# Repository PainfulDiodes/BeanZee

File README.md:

# BeanZee Z80 homebrew development board
A small Z80 based single-board-computer designed for experimentation.

Z80 CPU, 10 MHz clock, a simple reset circuit, 32K ROM, 32K RAM, FTDI UM245R USB module and the necessary glue logic.

Connectors provided for interfacing with the Z80: address, data, read, write, IO request, memory request, clock and reset.

The internal clock may be overridden by an external clock, and the internal memory and USB module may also be disabled via jumpers so that external devices can be used, or additional memory and IO selection logic added.

There is an accompanying [Marvin](https://github.com/PainfulDiodes/marvin) simple monitor program which can be used to inspect and modify memory contents and load and execute a program from the host computer. Example programs can be found in [BeanZeeBytes](https://github.com/PainfulDiodes/BeanZeeBytes).

See also:  
* [Detailed README](README-DETAILED.md)   
* [QWERTY Keyboard, simple LCD display and GPIO for BeanZee](https://github.com/PainfulDiodes/BeanBoard)  
* [MINT minimalist interpreter for BeanZee](https://github.com/PainfulDiodes/MINT)  
* [Blog post](https://painfuldiodes.wordpress.com/2024/12/29/beanzee-z80-development-board/)  
* [Hackaday project](https://hackaday.io/project/202193-beanzee)  
    
<br>
<br>

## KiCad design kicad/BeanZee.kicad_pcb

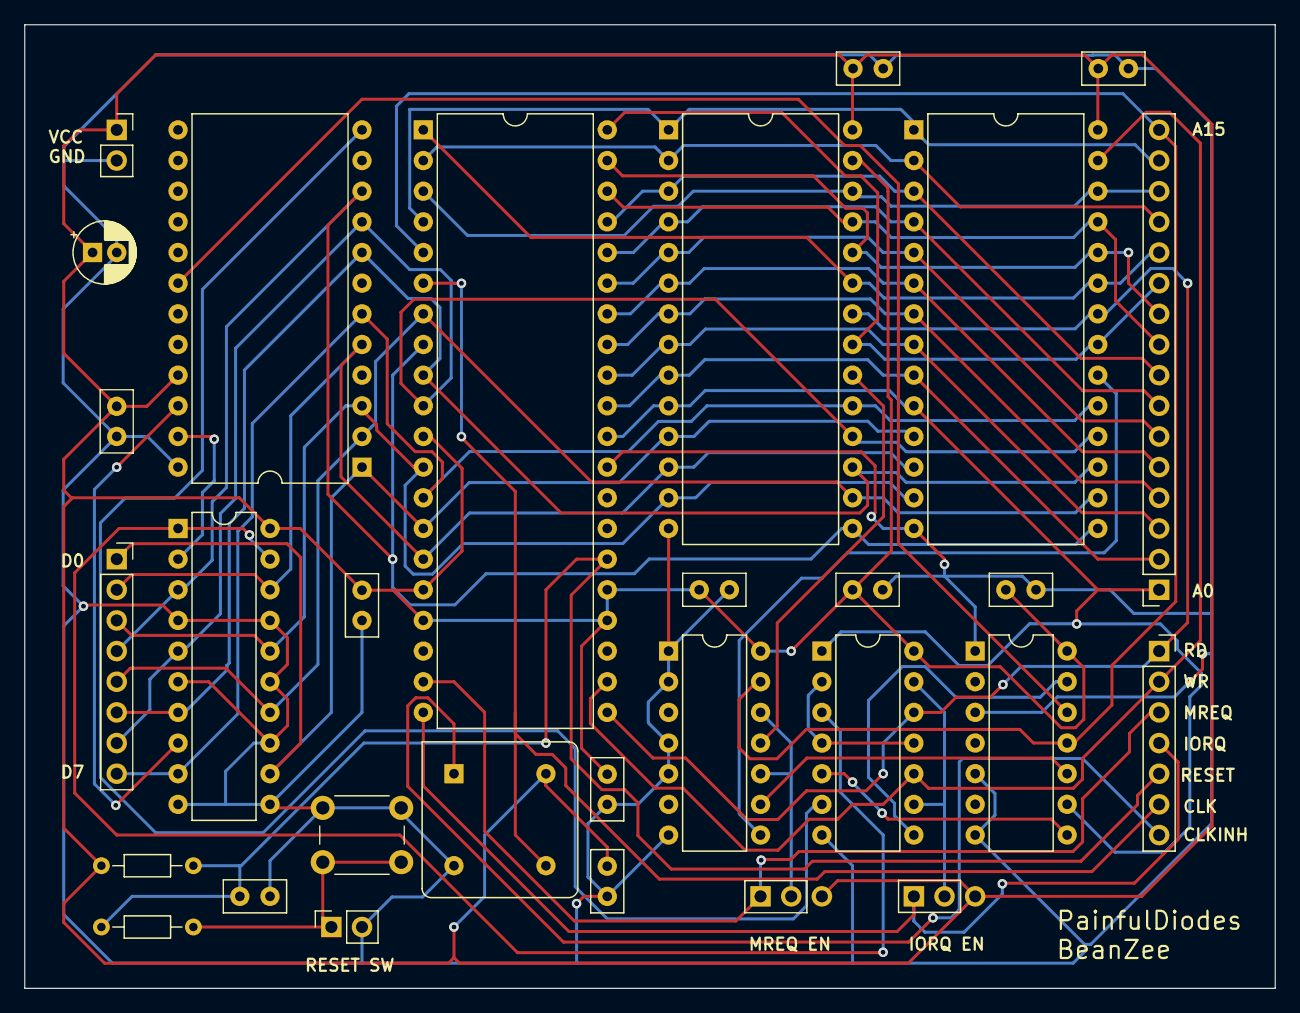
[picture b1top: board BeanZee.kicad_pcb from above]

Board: 2 copper layers, 103.6 x 79.8 mm, 30 parts (0 on the bottom side), 47 nets.

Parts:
C1, C2, C4, C5, C6, C7, C8, C9, C10, C11: 0.1uF; C_Disc_D5.0mm_W2.5mm_P2.50mm
C3: 100uF; CP_Radial_D5.0mm_P2.00mm
J1: Address; PinSocket_1x16_P2.54mm_Vertical
J2: Data; PinSocket_1x08_P2.54mm_Vertical
J3: Control; PinSocket_1x07_P2.54mm_Vertical
J4: Power; PinSocket_1x02_P2.54mm_Vertical
J5: Reset; PinSocket_1x02_P2.54mm_Vertical
JP1: IORQ_enable; PinHeader_1x03_P2.54mm_Vertical
JP2: MREQ_enable; PinHeader_1x03_P2.54mm_Vertical
R1: 220R; R_Axial_DIN0204_L3.6mm_D1.6mm_P7.62mm_Horizontal
R2: 10k; R_Axial_DIN0204_L3.6mm_D1.6mm_P7.62mm_Horizontal
SW1: Reset; SW_PUSH_6mm_H5mm
U1: 74LS244; DIP-20_W7.62mm
U2, U4: 74LS32; DIP-14_W7.62mm
U3: 74LS04; DIP-14_W7.62mm
U5: Z80CPU; DIP-40_W15.24mm
U6: AT28C256 (32kB ROM); DIP-28_W15.24mm
U7: UM245R; DIP-24_W15.24mm
U8: ECS-2200B-100 10MHz; Oscillator_DIP-8
U9: AS6C62256 (32kB SRAM); DIP-28_W15.24mm

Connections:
/A0: J1.1, U3.9, U4.1, U5.30 (A0), U6.10 (A0), U9.10 (A0)
/A1: J1.2, U5.31 (A1), U6.9 (A1), U9.9 (A1)
/A2: J1.3, U5.32 (A2), U6.8 (A2), U9.8 (A2)
/A3: J1.4, U5.33 (A3), U6.7 (A3), U9.7 (A3)
/A4: J1.5, U5.34 (A4), U6.6 (A4), U9.6 (A4)
/A5: J1.6, U5.35 (A5), U6.5 (A5), U9.5 (A5)
/A6: J1.7, U5.36 (A6), U6.4 (A6), U9.4 (A6)
/A7: J1.8, U5.37 (A7), U6.3 (A7), U9.3 (A7)
/A8: J1.9, U5.38 (A8), U6.25 (A8), U9.25 (A8)
/A9: J1.10, U5.39 (A9), U6.24 (A9), U9.24 (A9)
/A10: J1.11, U5.40 (A10), U6.21 (A10), U9.21 (A10)
/A11: J1.12, U5.1 (A11), U6.23 (A11), U9.23 (A11)
/A12: J1.13, U5.2 (A12), U6.2 (A12), U9.2 (A12)
/A13: J1.14, U5.3 (A13), U6.26 (A13), U9.26 (A13)
/A14: J1.15, U5.4 (A14), U6.1 (A14), U9.1 (A14)
/A15: J1.16, U2.13, U3.11, U5.5 (A15)
/D0: J2.1, U1.12 (O3a), U5.14 (D0), U6.11 (D0), U7.1 (D0), U9.11 (D0)
/D1: J2.2, U1.18 (O0a), U5.15 (D1), U6.12 (D1), U7.5 (D1), U9.12 (D1)
/D2: J2.3, U1.16 (O1a), U5.12 (D2), U6.13 (D2), U7.3 (D2), U9.13 (D2)
/D3: J2.4, U1.3 (O3b), U5.8 (D3), U6.15 (D3), U7.10 (D3), U9.15 (D3)
/D4: J2.5, U1.14 (O2a), U5.7 (D4), U6.16 (D4), U7.2 (D4), U9.16 (D4)
/D5: J2.6, U1.7 (O1b), U5.9 (D5), U6.17 (D5), U7.8 (D5), U9.17 (D5)
/D6: J2.7, U1.5 (O2b), U5.10 (D6), U6.18 (D6), U7.9 (D6), U9.18 (D6)
/D7: J2.8, U1.9 (O0b), U5.13 (D7), U6.19 (D7), U7.6 (D7), U9.19 (D7)
/P0D0: U1.8 (I3a), U7.22 (~TXE)
/P0D1: U1.2 (I0a), U7.23 (~RXF)
/WR_PORT_1: U3.12, U7.18 (WR)
/~A15: U2.9, U3.10
/~CLKINH: J3.7, U8.1 (Tri-State)
/~CLK: J3.6, U5.6 (~CLK), U8.5 (OUT)
/~IORQ: J3.4, JP1.1 (A), U5.20 (~IORQ)
/~MREQ: J3.3, JP2.1 (A), U5.19 (~MREQ)
/~RAM_CE: U2.8, U9.20 (~CE)
/~RD_PORT_0: U1.1 (OEa), U1.19 (OEb), U4.3
/~RD_PORT_1: U4.6, U7.12 (~RD)
/~RD: J3.1, U4.12, U5.21 (~RD), U6.22 (~OE), U9.22 (~OE)
/~RESET: C1.1, J3.5, R1.1, R2.2, U5.26 (~RESET)
/~ROM_CE: U2.11, U6.20 (~CE)
/~WR: J3.2, U4.10, U5.22 (~WR), U9.27 (~WE)
GND: C1.2, C2.2, C3.2, C4.2, C5.2, C6.2, C7.2, C8.2, C9.2, C10.2, C11.2, J4.2, J5.2, SW1.1, U1.4 (I1a), U1.6 (I2a), U1.10 (GND), U1.11 (I0b), U1.13 (I1b), U1.15 (I2b), U1.17 (I3b), U2.1, U2.2, U2.4, U2.5, U2.7 (GND), U3.1, U3.3, U3.5, U3.7 (GND), U4.7 (GND), U5.29 (GND), U6.14 (GND), U7.24 (GND), U8.4 (GND), U9.14 (VSS)
unnamed: J5.1, R1.2, SW1.2
unnamed: JP1.2 (C), U4.9, U4.13
unnamed: JP2.2 (C), U2.10, U2.12
unnamed: U3.8, U4.5
unnamed: U3.13, U4.8
unnamed: U4.2, U4.4, U4.11
VCC: C2.1, C3.1, C4.1, C5.1, C6.1, C7.1, C8.1, C9.1, C10.1, C11.1, J4.1, JP1.3 (B), JP2.3 (B), R2.1, U1.20 (VCC), U2.14 (VCC), U3.14 (VCC), U4.14 (VCC), U5.11 (VCC), U5.16 (~INT), U5.17 (~NMI), U5.24 (~WAIT), U5.25 (~BUSRQ), U6.27 (~WE), U6.28 (VCC), U7.21 (VCC), U8.8 (VDD), U9.28 (VCC)

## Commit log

2024-12-28 format schematic
2024-12-28 Add schematic images
2024-12-28 Reformat schematic
2024-12-29 Split schematic
2024-12-30 Add simplified PCB layout image
2025-01-31 Prototype KiCAD
2025-02-27 Update READMEs
    Marvin 1.0.0 features
